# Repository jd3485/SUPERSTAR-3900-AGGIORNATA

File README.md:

# SUPERSTAR 3900 CON AGGIORNAMENTI

**Progetto radio Connex / Superstar 3900 aggiornato · due PCB THT MAIN + FRONT · KiCad · montaggio manuale PCBWay**

> **STATO 19 novembre 2026 — CAD CANDIDATO, NON FABBRICABILE.** La home `main` contiene documentazione e indici. Schemi e PCB effettivi si trovano nella [PR #1 in bozza](https://github.com/jd3485/SUPERSTAR-3900-AGGIORNATA/pull/1), ramo `cad/avvio-main-front`. **Non ancora integrati su main.**

## Cruscotto avanzamento

| Area | Stato verificato | Percorso |
|---|---|---|
| Mandato / regole | Documentazione integrata su `main` | [AGENTS.md](AGENTS.md) |
| Specifiche funzionali | REQ-01–14 **candidate sul ramo PR** | [Indice specifiche](01_Specifiche/README.md) |
| PCB MAIN | Schema e PCB candidate; **44 impronte THT presenti**, 18 ancora mancanti nel checkpoint | [Indice KiCad](KiCad/README.md) |
| PCB FRONT | Schema e PCB candidate; **4 componenti** posizionati e collegati | [Indice KiCad](KiCad/README.md) |
| Filtri RX / conversione / IF AM | Primi stadi progettati, modelli e netlist preliminari; non validati al banco | [Percorso RX candidato](https://github.com/jd3485/SUPERSTAR-3900-AGGIORNATA/tree/cad/avvio-main-front/KiCad/RX) |
| Sintonia | Mappa candidata di 240 canali base; estensioni a 271 da verificare | [Sintonia candidata](https://github.com/jd3485/SUPERSTAR-3900-AGGIORNATA/tree/cad/avvio-main-front/KiCad/Sintonia) |
| Verifiche CAD | **ERC MAIN 10 errori; FRONT 4**; DRC diagnostici, non finali | [Indice verifiche](Verifiche/README.md) |
| PCBWay / prototipo | **NON AUTORIZZATO**; nessuna PCB produttiva pronta | [Sicurezza](AGENTS.md#sicurezza) |

I numeri della MAIN/FRONT riportano l'**ultimo checkpoint del ramo candidato**, non la versione approvata di `main`. Un pad collegato nel layout parziale non equivale a scheda completa o validata.

## Versioni / milestone

| Milestone | Descrizione | Stato |
|---|---|---|
| **V0.0 — Bootstrap** | Direttiva, checkpoint, ingresso di ripresa | **Su `main`** |
| **V0.1 — MAIN/FRONT WIP** | Requisiti, primi schemi, prime PCB, PTT, alimentazione logica, RX/IF | **PR #1 DRAFT, NON MERGED** |
| **V0.2 — Integrazione tecnica** | Completamento dei percorsi e delle interfacce, qualifiche e regressioni | **Da realizzare** |
| **V1.0 — CAD pronto alla revisione di fabbricazione** | Schemi e PCB complete, ERC/DRC applicabili, BOM OEM, verifica indipendente | **Non raggiunta** |

Queste sigle sono **milestone organizzative** e non indicano versioni CAD rilasciate. La storia tecnica resta nei commit, nella PR e nel checkpoint.

## Navigazione repository

- [00_Gestione_Progetto — stato canonico e direttive](00_Gestione_Progetto/WORK_STATO_CORRENTE.md)
- [01_Specifiche — requisiti e decisioni](01_Specifiche/README.md)
- [KiCad — MAIN / FRONT / RX / Sintonia](KiCad/README.md)
- [Verifiche — ERC, netlist, DRC, modelli](Verifiche/README.md)
- [AGENTS.md — mandato, controlli e autorizzazioni](AGENTS.md)
- [PR #1 — lavoro CAD in corso](https://github.com/jd3485/SUPERSTAR-3900-AGGIORNATA/pull/1)

## Prossimi passi

Completare la catena RF/IF e la scelta del dispositivo RF THT secondo rumore, blocco e intermodulazione; chiudere alimentazioni, PTT e connessioni tra schede; trasferire sul PCB le impronte mancanti; qualificare componenti OEM attivi; correggere gli ERC, completare le PCB e verificare i DRC. Integrare la PR solo rispettando i gate e le autorizzazioni previsti.

**Vincoli permanenti:** NO FAB · NO GERBER DI PRODUZIONE · NO ORDINI PCB · NO TX · NO BATTERIA · NO VEICOLO, finché non espressamente autorizzati dopo le verifiche.

### Ripresa da una nuova chat

«Riprendi `jd3485/SUPERSTAR-3900-AGGIORNATA` da `main`, leggi `AGENTS.md`, `00_Gestione_Progetto/WORK_STATO_CORRENTE.md` e la PR aperta, verifica lo SHA reale e procedi».

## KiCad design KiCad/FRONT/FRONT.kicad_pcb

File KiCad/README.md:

# KiCad — Schemi e PCB native

**Su `main`:** nessuna scheda CAD integrata al momento di questo indice.

**Su ramo candidato [`cad/avvio-main-front`](https://github.com/jd3485/SUPERSTAR-3900-AGGIORNATA/tree/cad/avvio-main-front/KiCad):**

- [MAIN — schema](https://github.com/jd3485/SUPERSTAR-3900-AGGIORNATA/blob/cad/avvio-main-front/KiCad/MAIN/MAIN.kicad_sch) · [MAIN — PCB](https://github.com/jd3485/SUPERSTAR-3900-AGGIORNATA/blob/cad/avvio-main-front/KiCad/MAIN/MAIN.kicad_pcb)
- [FRONT — schema](https://github.com/jd3485/SUPERSTAR-3900-AGGIORNATA/blob/cad/avvio-main-front/KiCad/FRONT/FRONT.kicad_sch) · [FRONT — PCB](https://github.com/jd3485/SUPERSTAR-3900-AGGIORNATA/blob/cad/avvio-main-front/KiCad/FRONT/FRONT.kicad_pcb)
- [Percorso RX/IF](https://github.com/jd3485/SUPERSTAR-3900-AGGIORNATA/tree/cad/avvio-main-front/KiCad/RX) · [Sintonia](https://github.com/jd3485/SUPERSTAR-3900-AGGIORNATA/tree/cad/avvio-main-front/KiCad/Sintonia) · [Interfaccia MAIN–FRONT](https://github.com/jd3485/SUPERSTAR-3900-AGGIORNATA/blob/cad/avvio-main-front/KiCad/INTERFACCIA_MAIN_FRONT.md)

**Non fabbricabile:** contorni, componenti, connessioni, alimentazioni, ERC e qualifica ancora incompleti. Nessun Gerber produttivo autorizzato.

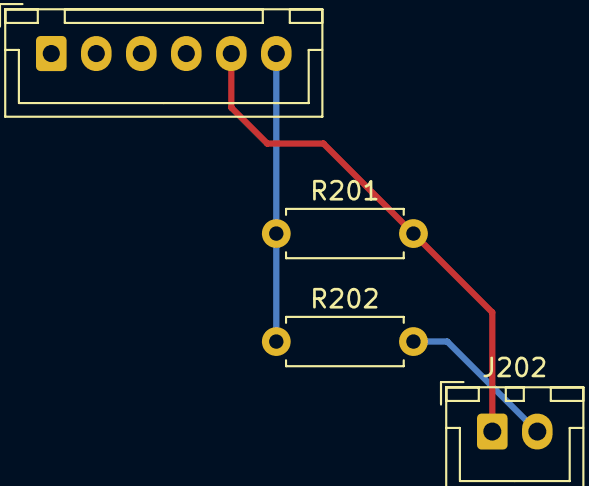
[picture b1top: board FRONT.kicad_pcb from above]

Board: 2 copper layers, 4 parts (0 on the bottom side), 3 nets.

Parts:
J201: Conn_01x06; JST_XH_B6B-XH-A_1x06_P2.50mm_Vertical
J202: Conn_01x02; JST_XH_B2B-XH-A_1x02_P2.50mm_Vertical
R201: 10k; R_Axial_DIN0207_L6.3mm_D2.5mm_P7.62mm_Horizontal
R202: 2.2k; R_Axial_DIN0207_L6.3mm_D2.5mm_P7.62mm_Horizontal

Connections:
/CONTROL_RETURN: J201.5, J202.1, R201.2
/MIC_PTT_KEY: J202.2, R202.2
/PTT_SENSE: J201.6, R201.1, R202.1

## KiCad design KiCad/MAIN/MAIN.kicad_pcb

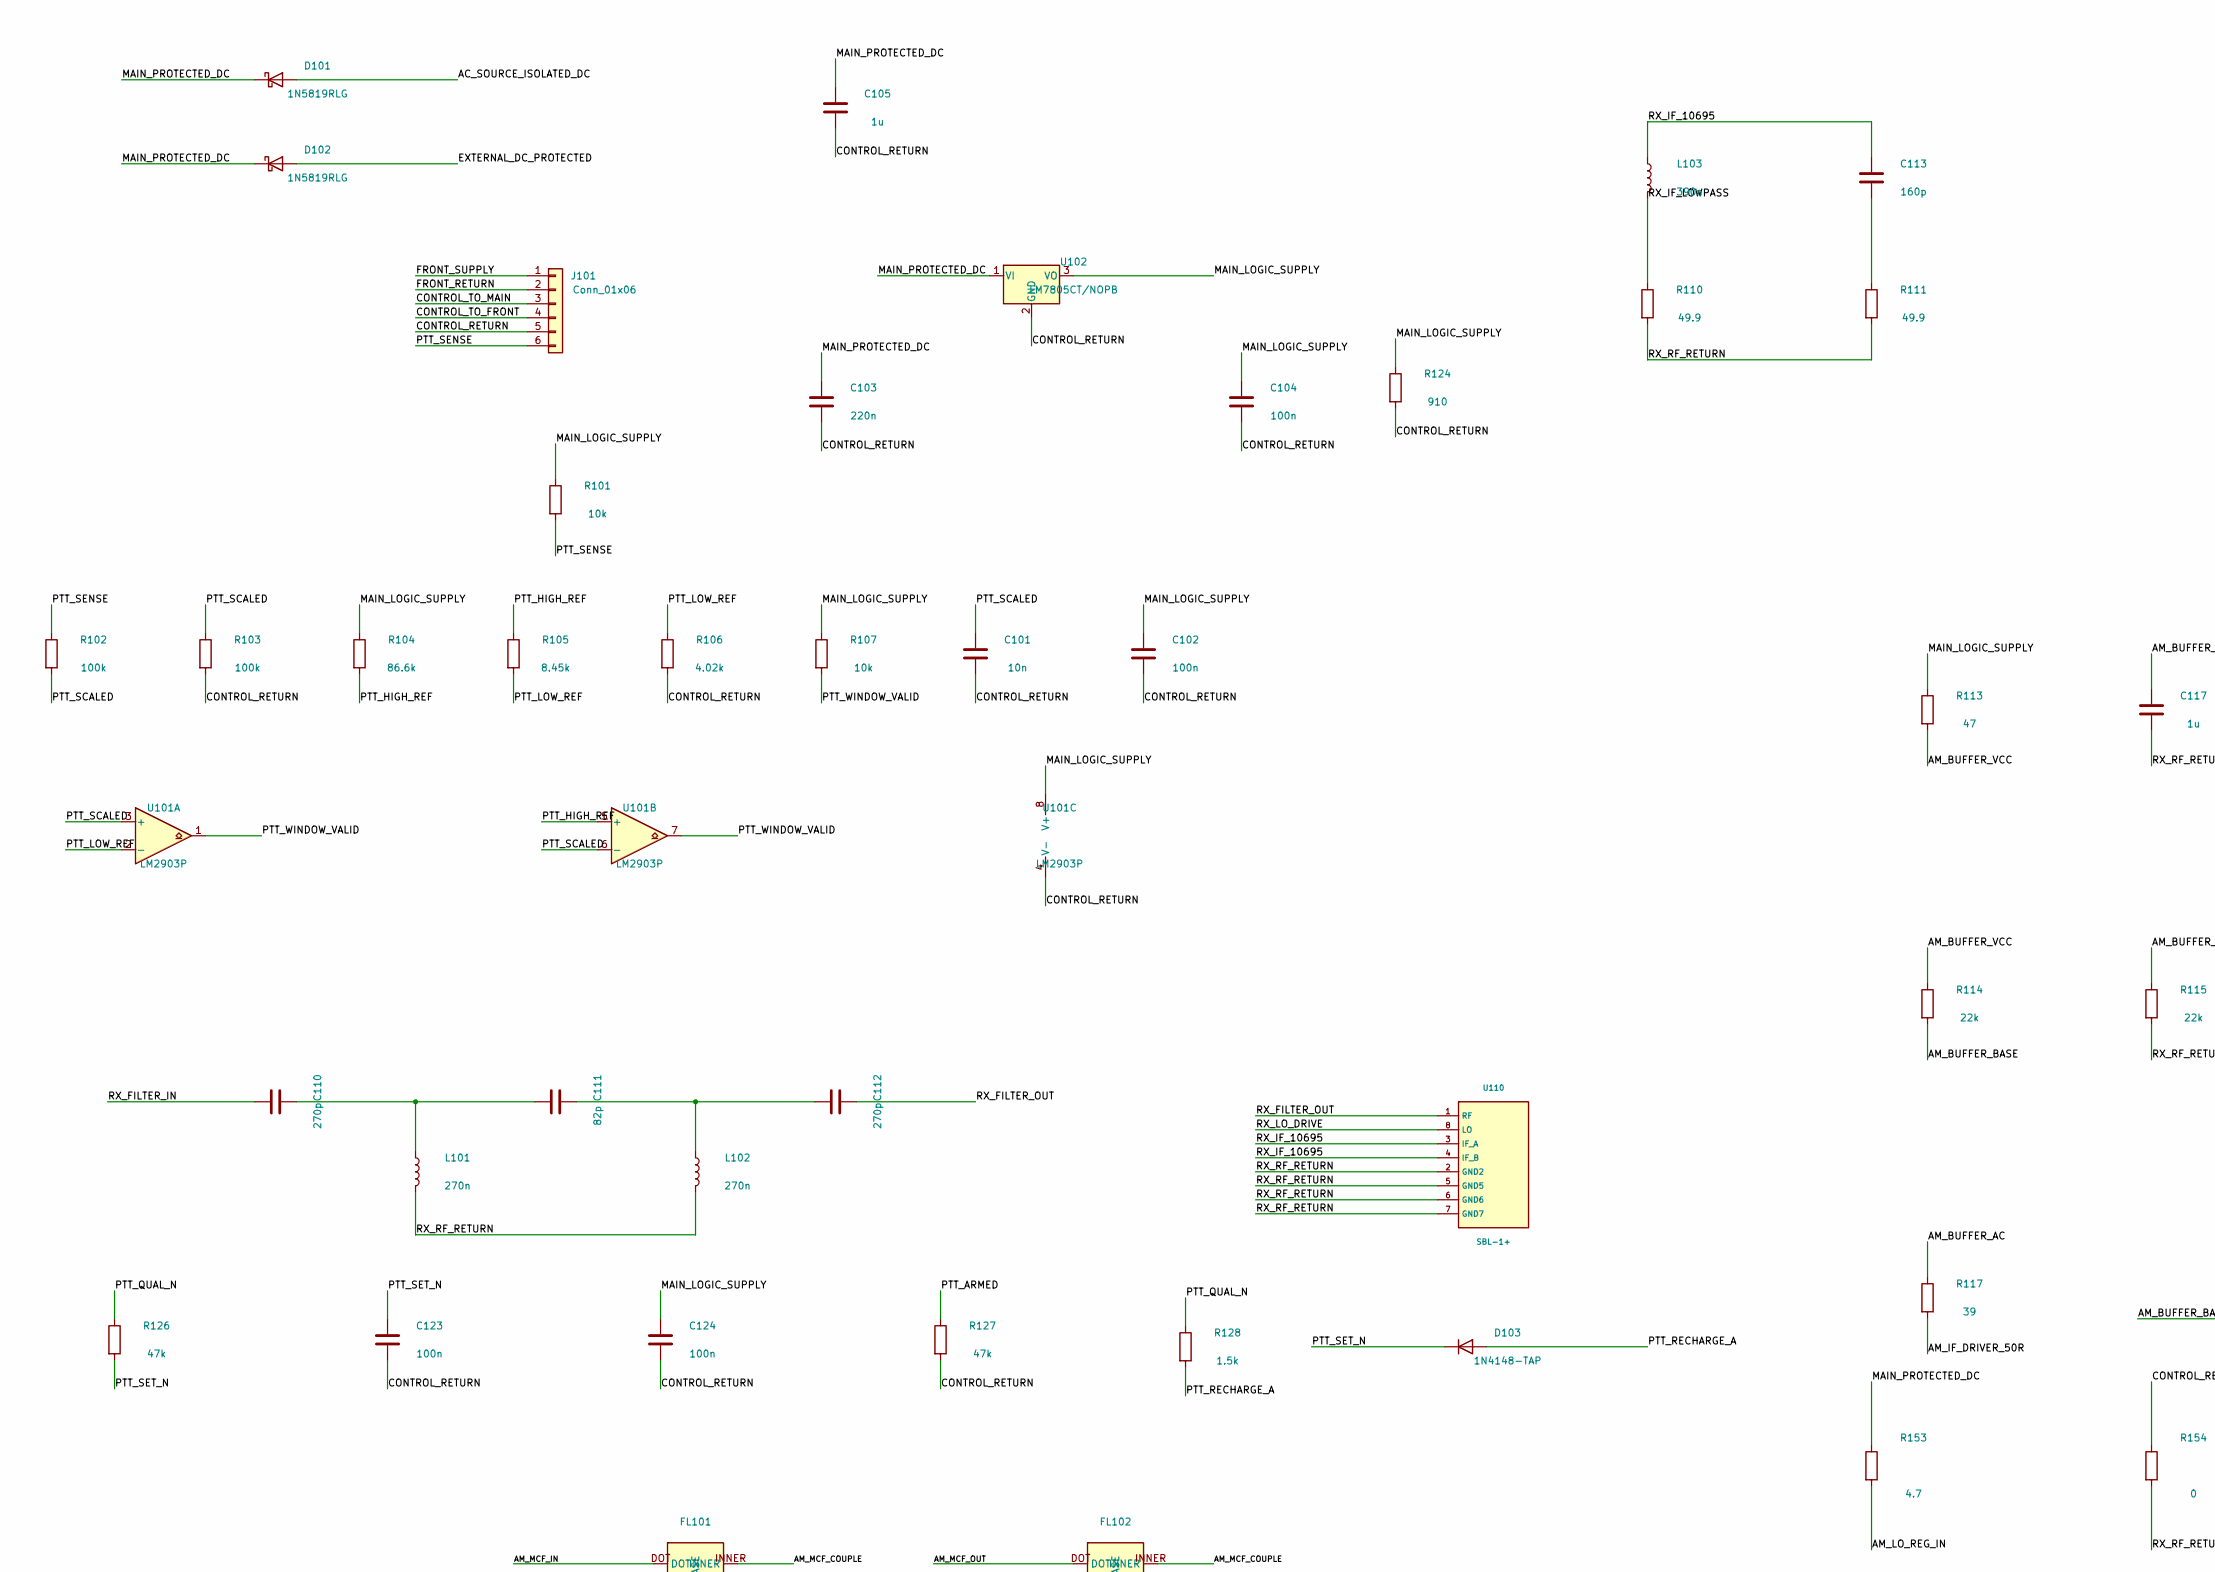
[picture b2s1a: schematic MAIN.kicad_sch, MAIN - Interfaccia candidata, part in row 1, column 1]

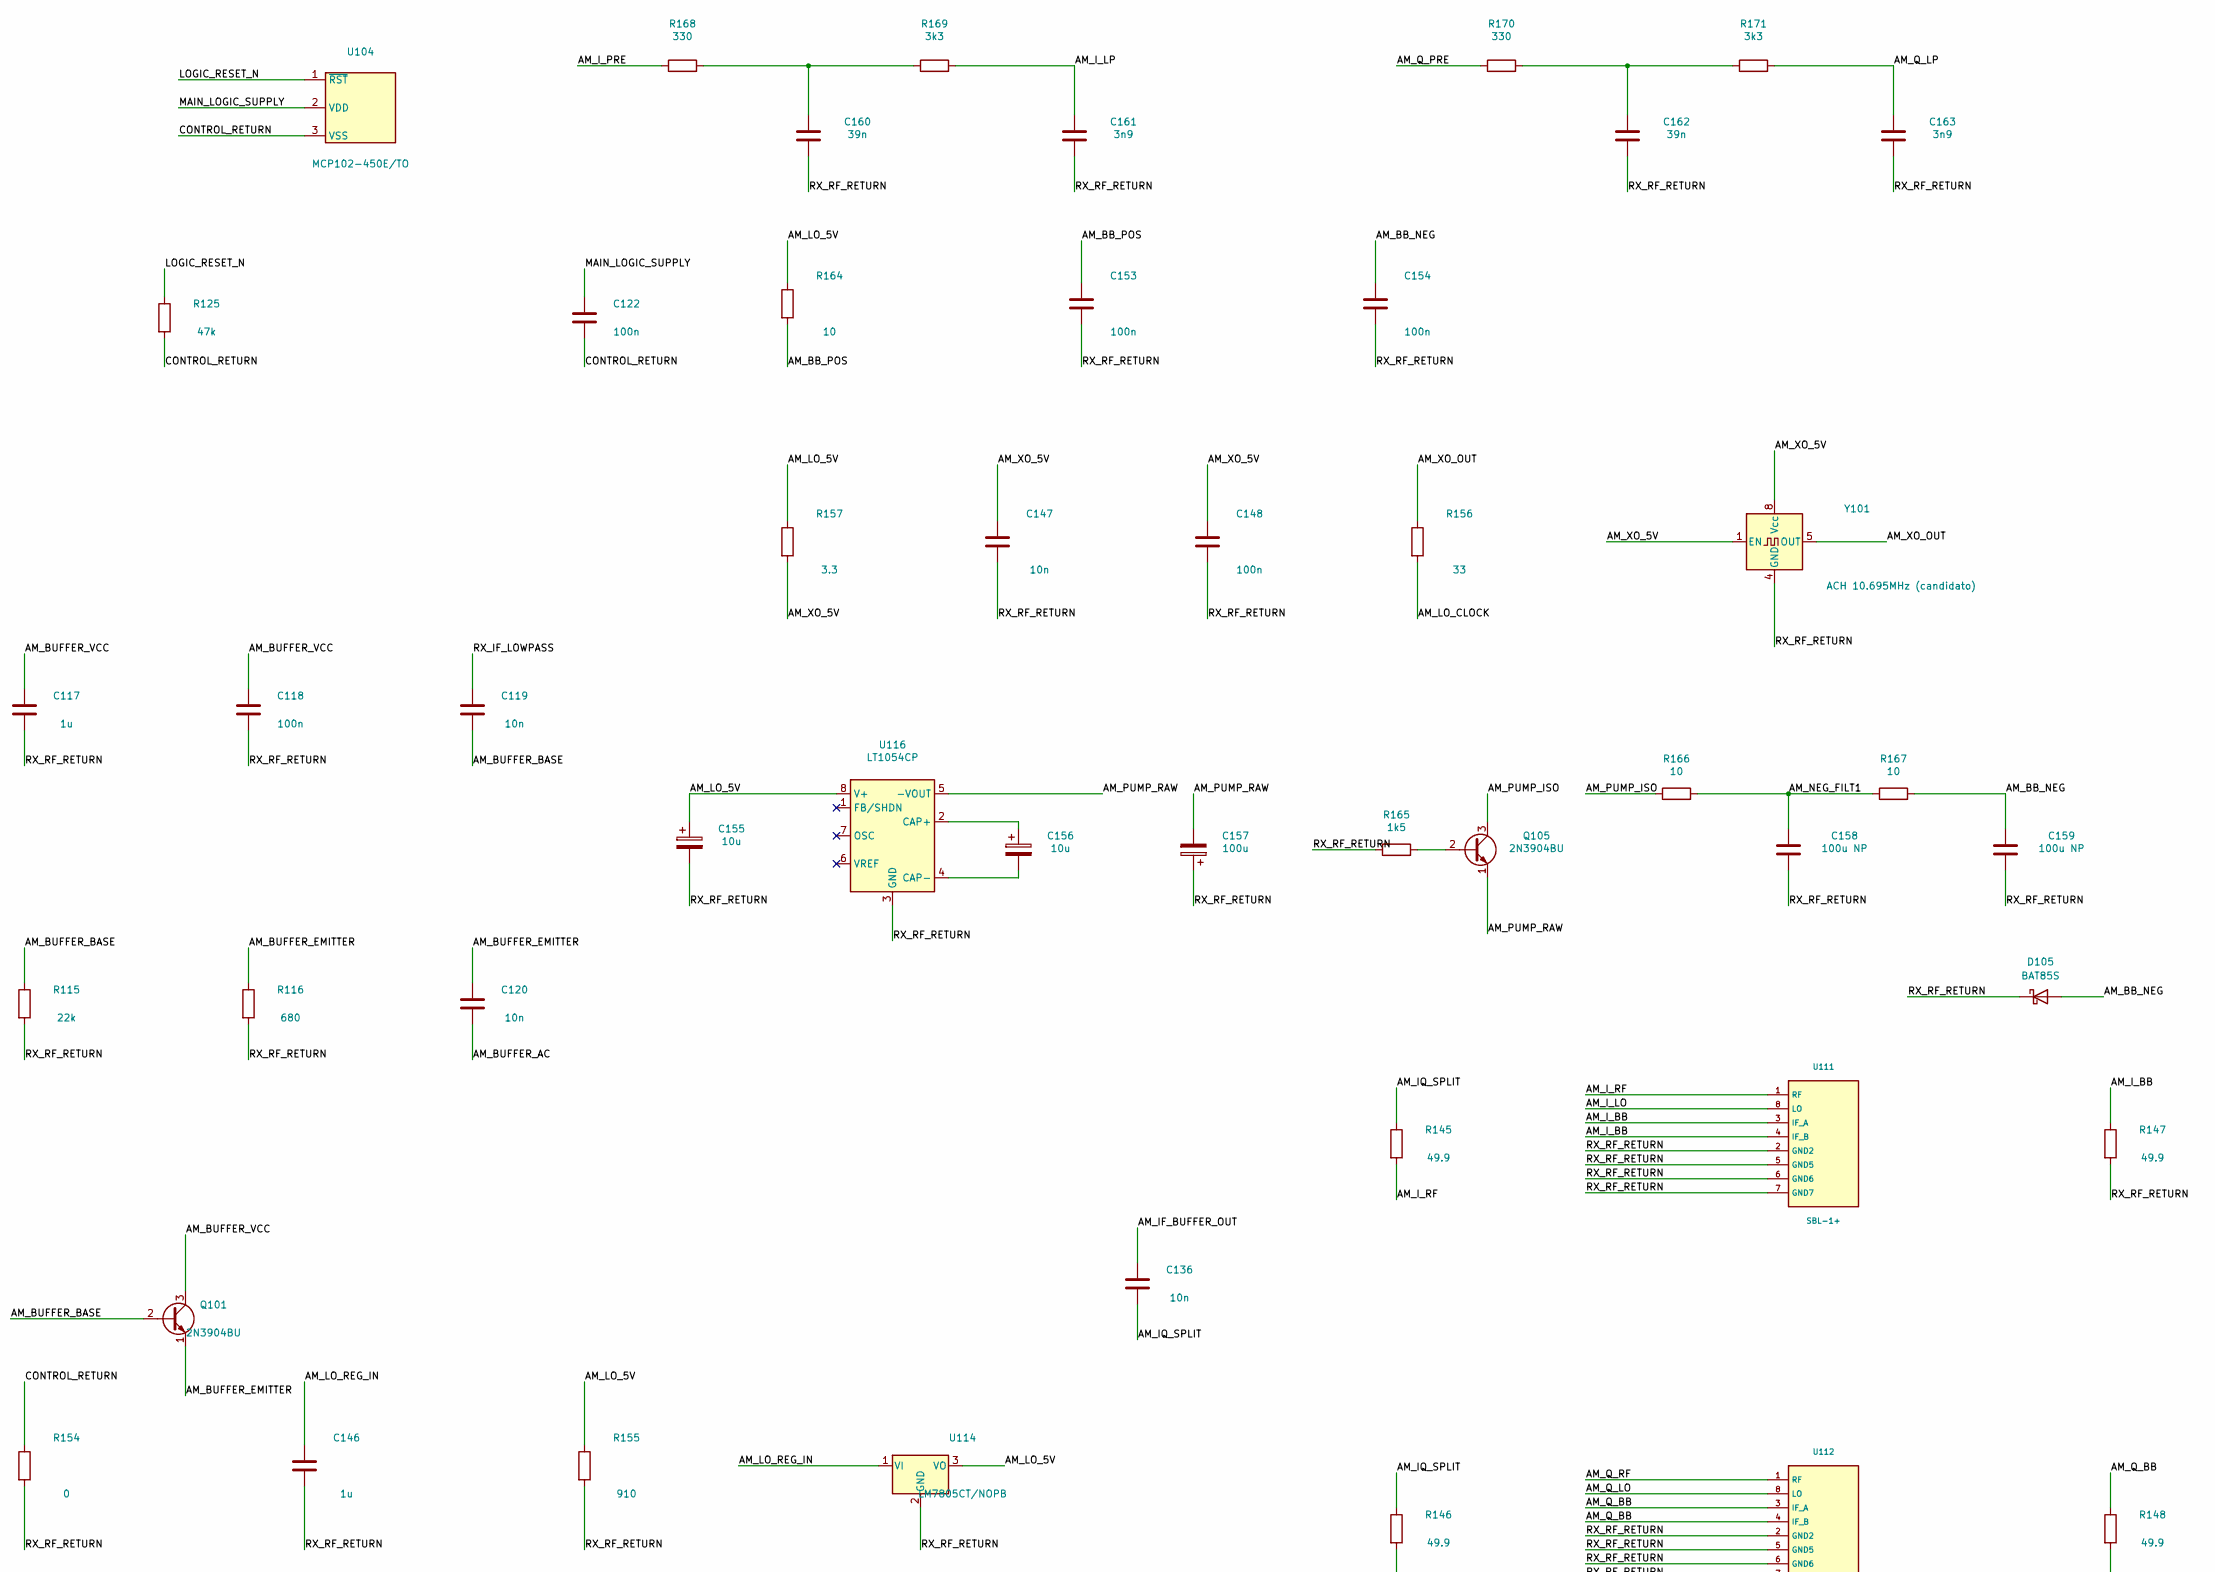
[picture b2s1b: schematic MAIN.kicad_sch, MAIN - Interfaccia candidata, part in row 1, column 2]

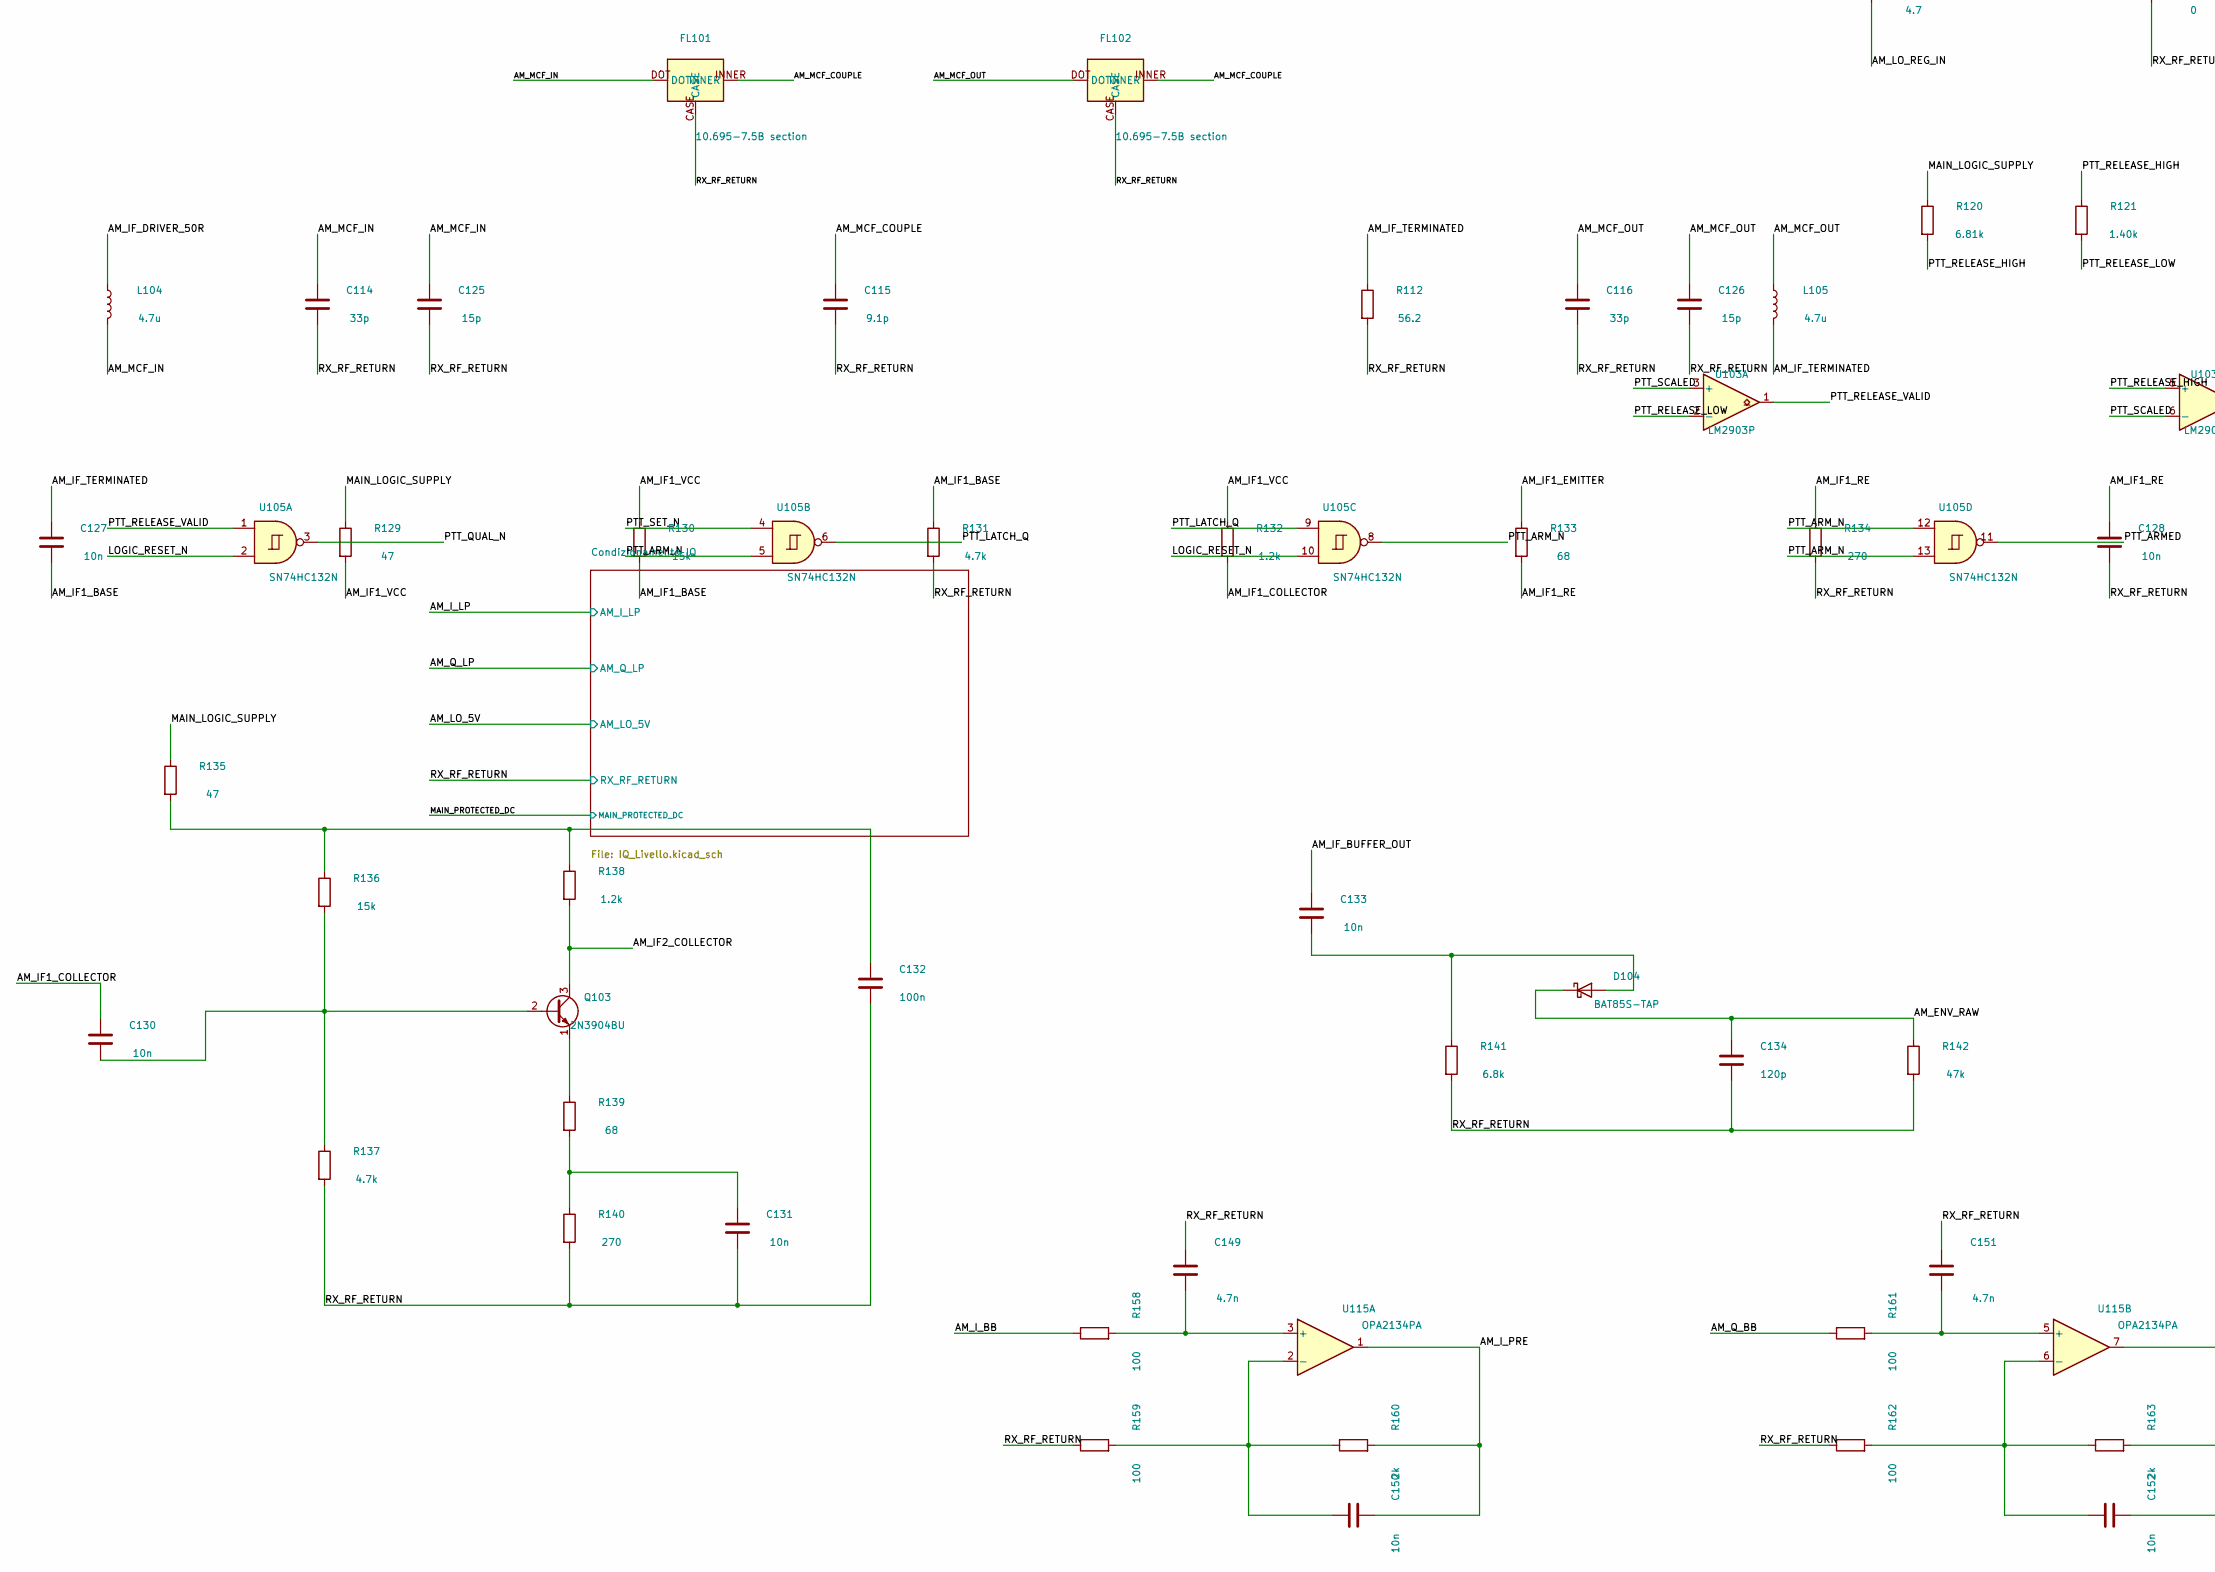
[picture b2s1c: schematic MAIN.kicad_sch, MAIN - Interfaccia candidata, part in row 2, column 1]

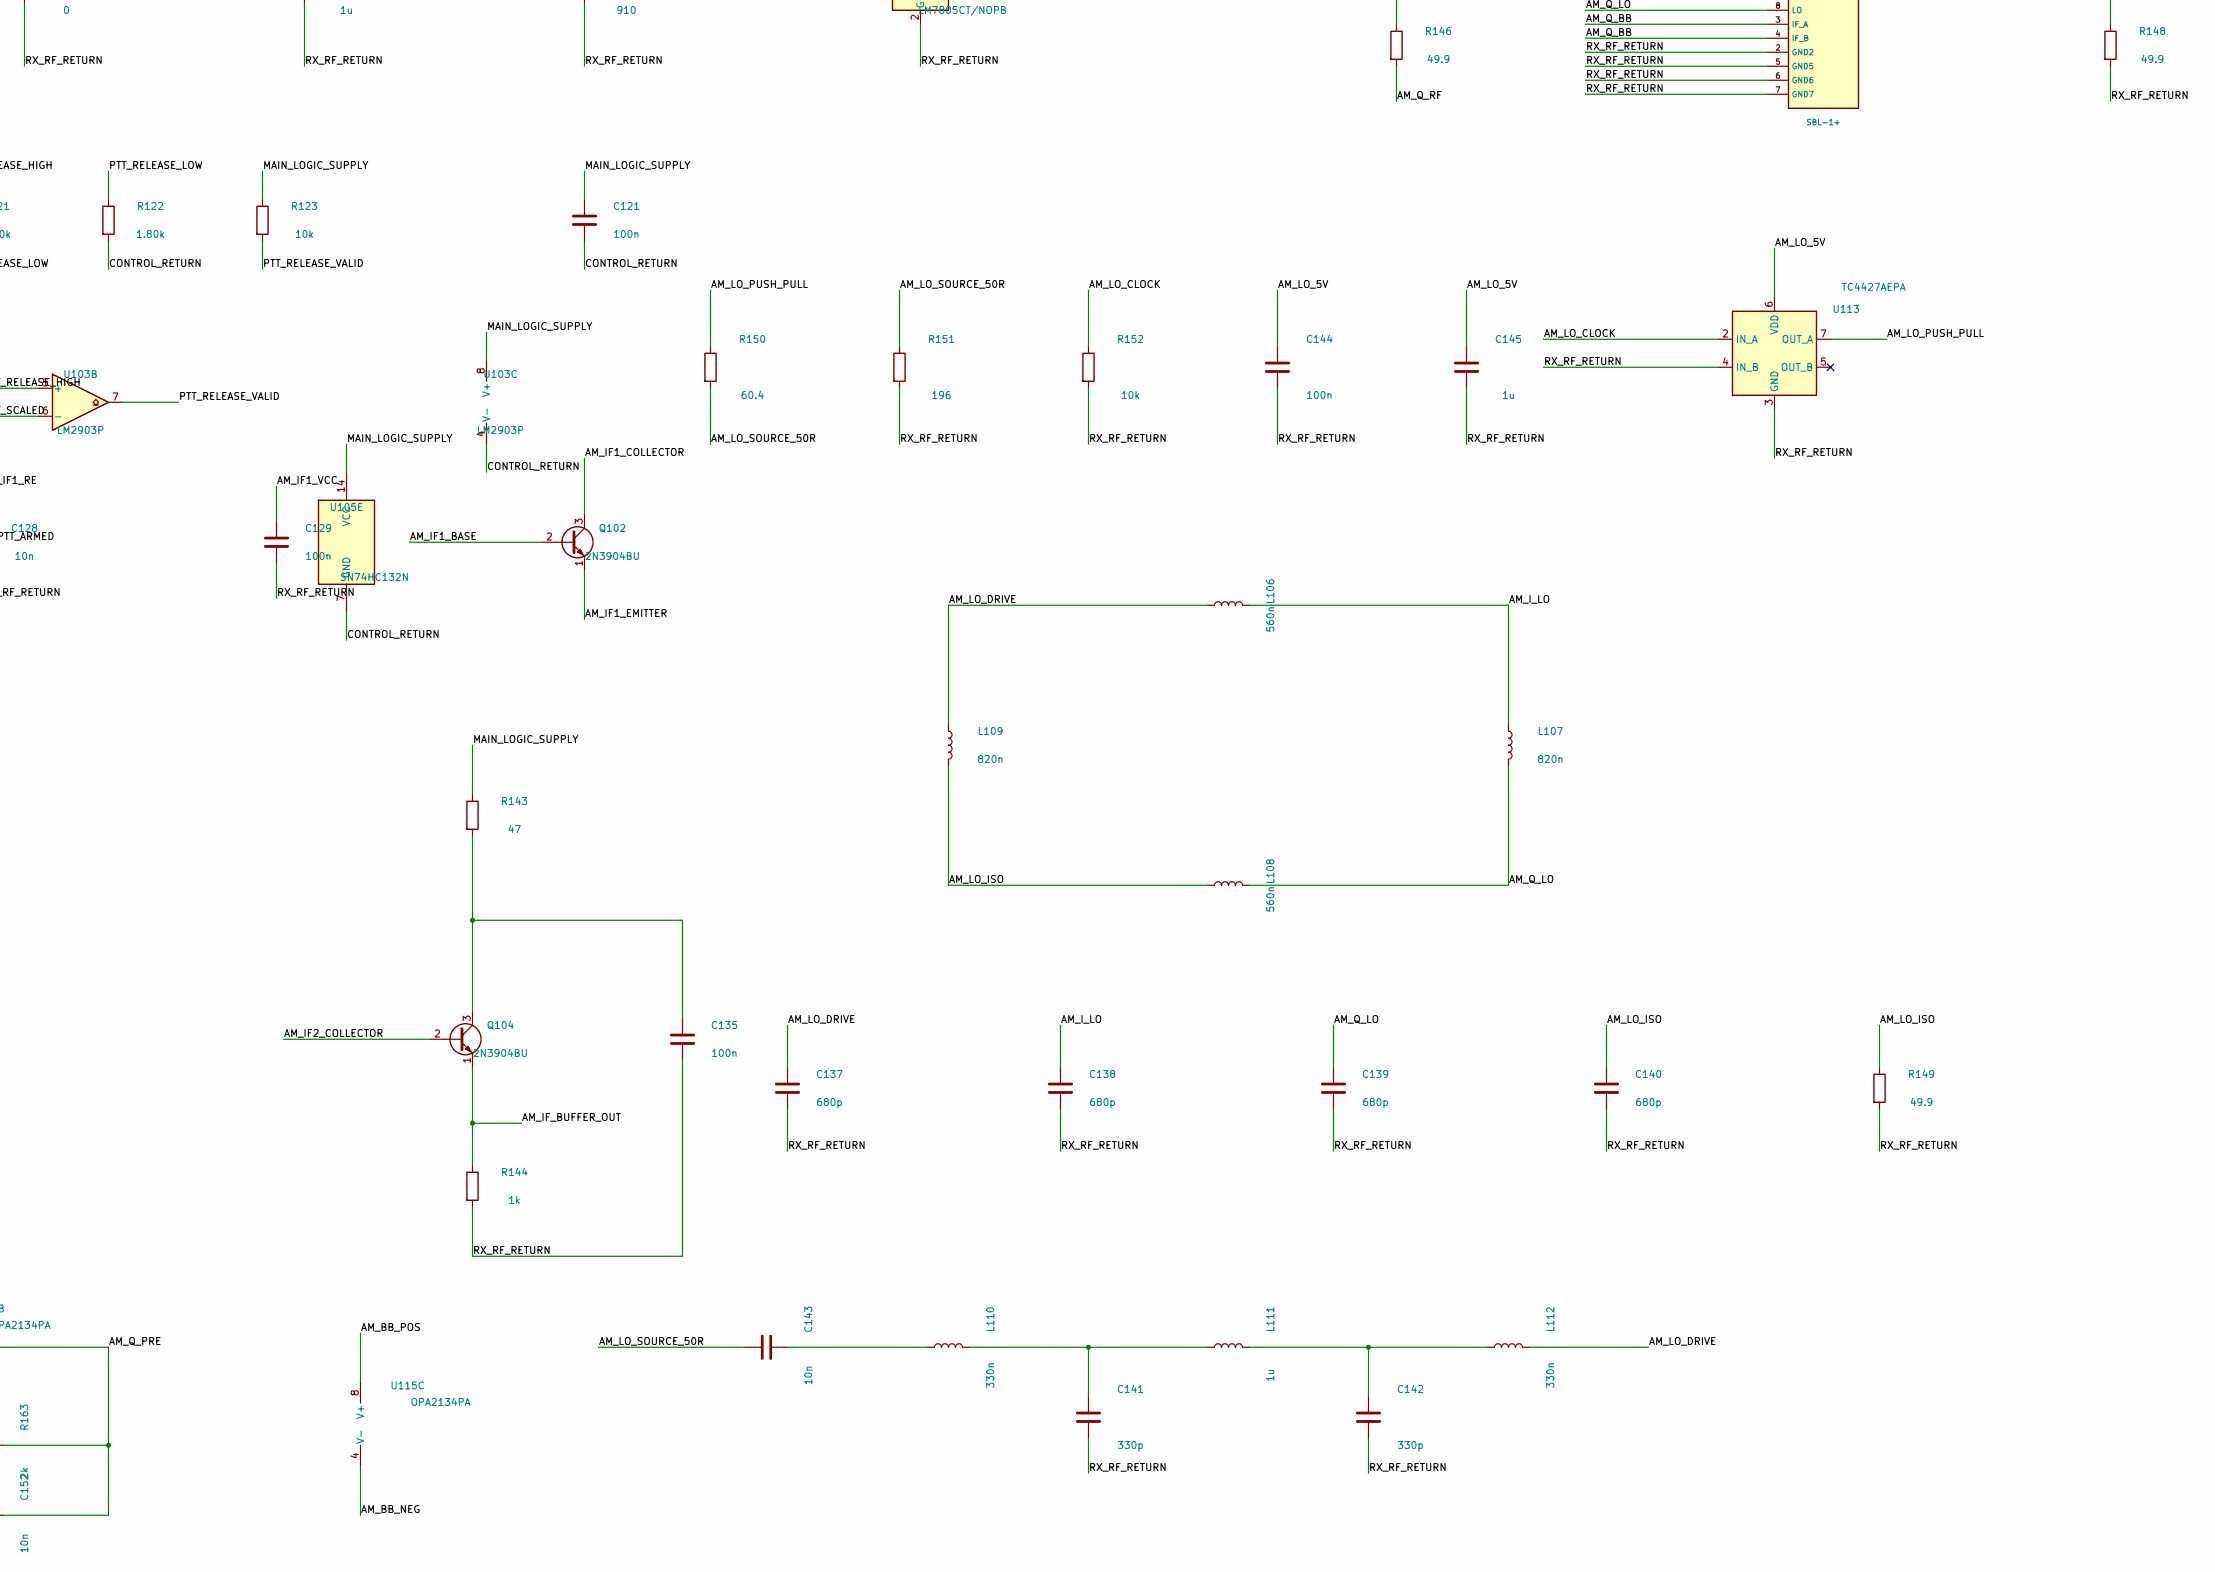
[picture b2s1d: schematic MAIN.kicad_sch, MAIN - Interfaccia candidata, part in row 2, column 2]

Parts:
C101, C119, C120, C127, C128, C130, C131, C133, C136, C143, C147, C150, C152: 10n; C_Rect_L4.0mm_W2.5mm_P2.50mm
C102, C104, C118, C121, C122, C123, C124, C129, C132, C135, C144, C148, C153, C154: 100n; C_Rect_L4.0mm_W2.5mm_P2.50mm
C103: 220n; C_Rect_L4.0mm_W2.5mm_P2.50mm
C105, C117, C146: 1u; C_Rect_L7.0mm_W4.5mm_P5.00mm
C110, C112: 270p; C_Rect_L4.0mm_W2.5mm_P2.50mm
C111: 82p; C_Rect_L4.0mm_W2.5mm_P2.50mm
C113: 160p; C_Rect_L4.0mm_W2.5mm_P2.50mm
C114, C116: 33p; C_Rect_L4.0mm_W2.5mm_P2.50mm
C115: 9.1p; C_Rect_L4.0mm_W2.5mm_P2.50mm
C125, C126: 15p; C_Rect_L4.0mm_W2.5mm_P2.50mm
C134: 120p; C_Rect_L4.0mm_W2.5mm_P2.50mm
C137, C138, C139, C140: 680p; C_Rect_L4.0mm_W2.5mm_P2.50mm
C141, C142: 330p; C_Rect_L4.0mm_W2.5mm_P2.50mm
C145: 1u; C_Rect_L4.0mm_W2.5mm_P2.50mm
C149, C151: 4.7n; C_Rect_L4.0mm_W2.5mm_P2.50mm
C155, C156: 10u; CP_Radial_D5.0mm_P2.00mm
C157: 100u; CP_Radial_D6.3mm_P2.50mm
C158, C159: 100u NP; C_Radial_D10.0mm_H16.0mm_P5.00mm
C160, C162: 39n; C_Rect_L7.0mm_W2.5mm_P5.00mm
C161, C163: 3n9; C_Rect_L7.0mm_W2.5mm_P5.00mm
D101, D102: 1N5819RLG; D_DO-41_SOD81_P7.62mm_Horizontal
D103: 1N4148-TAP; D_DO-35_SOD27_P7.62mm_Horizontal
D104: BAT85S-TAP; D_DO-35_SOD27_P7.62mm_Horizontal
D105: BAT85S; D_DO-35_SOD27_P7.62mm_Horizontal
FL101, FL102: 10.695-7.5B section; Krystaly_HC49U_3pin_MCF
J101: Conn_01x06; JST_XH_B6B-XH-A_1x06_P2.50mm_Vertical
L101, L102: 270n; L_Axial_L7.0mm_D3.3mm_P10.16mm_Horizontal_Fastron_MICC
L103: 390n; L_Axial_L9.5mm_D4.0mm_P12.70mm_Horizontal_Fastron_SMCC
L104, L105: 4.7u; L_Axial_L7.0mm_D3.3mm_P10.16mm_Horizontal_Fastron_MICC
L106, L108: 560n; L_Axial_L7.0mm_D3.3mm_P10.16mm_Horizontal_Fastron_MICC
L107, L109: 820n; L_Axial_L7.0mm_D3.3mm_P10.16mm_Horizontal_Fastron_MICC
L110, L112: 330n; L_Axial_L7.0mm_D3.3mm_P10.16mm_Horizontal_Fastron_MICC
L111: 1u; L_Axial_L7.0mm_D3.3mm_P10.16mm_Horizontal_Fastron_MICC
Q101, Q102, Q103, Q104, Q105: 2N3904BU; TO-92_Inline
R101, R107, R123, R152: 10k; R_Axial_DIN0207_L6.3mm_D2.5mm_P7.62mm_Horizontal
R102, R103: 100k; R_Axial_DIN0207_L6.3mm_D2.5mm_P7.62mm_Horizontal
R104: 86.6k; R_Axial_DIN0207_L6.3mm_D2.5mm_P7.62mm_Horizontal
R105: 8.45k; R_Axial_DIN0207_L6.3mm_D2.5mm_P7.62mm_Horizontal
R106: 4.02k; R_Axial_DIN0207_L6.3mm_D2.5mm_P7.62mm_Horizontal
R110, R111, R145, R146, R147, R148, R149: 49.9; R_Axial_DIN0207_L6.3mm_D2.5mm_P7.62mm_Horizontal
R112: 56.2; R_Axial_DIN0207_L6.3mm_D2.5mm_P7.62mm_Horizontal
R113, R129, R135, R143: 47; R_Axial_DIN0207_L6.3mm_D2.5mm_P7.62mm_Horizontal
R114, R115: 22k; R_Axial_DIN0207_L6.3mm_D2.5mm_P7.62mm_Horizontal
R116: 680; R_Axial_DIN0207_L6.3mm_D2.5mm_P7.62mm_Horizontal
R117: 39; R_Axial_DIN0207_L6.3mm_D2.5mm_P7.62mm_Horizontal
R120: 6.81k; R_Axial_DIN0207_L6.3mm_D2.5mm_P7.62mm_Horizontal
R121: 1.40k; R_Axial_DIN0207_L6.3mm_D2.5mm_P7.62mm_Horizontal
R122: 1.80k; R_Axial_DIN0207_L6.3mm_D2.5mm_P7.62mm_Horizontal
R124, R155: 910; R_Axial_DIN0207_L6.3mm_D2.5mm_P7.62mm_Horizontal
R125, R126, R127, R142: 47k; R_Axial_DIN0207_L6.3mm_D2.5mm_P7.62mm_Horizontal
R128: 1.5k; R_Axial_DIN0207_L6.3mm_D2.5mm_P7.62mm_Horizontal
R130, R136: 15k; R_Axial_DIN0207_L6.3mm_D2.5mm_P7.62mm_Horizontal
R131, R137: 4.7k; R_Axial_DIN0207_L6.3mm_D2.5mm_P7.62mm_Horizontal
R132, R138: 1.2k; R_Axial_DIN0207_L6.3mm_D2.5mm_P7.62mm_Horizontal
R133, R139: 68; R_Axial_DIN0207_L6.3mm_D2.5mm_P7.62mm_Horizontal
R134, R140: 270; R_Axial_DIN0207_L6.3mm_D2.5mm_P7.62mm_Horizontal
R141: 6.8k; R_Axial_DIN0207_L6.3mm_D2.5mm_P7.62mm_Horizontal
R144: 1k; R_Axial_DIN0207_L6.3mm_D2.5mm_P7.62mm_Horizontal
R150: 60.4; R_Axial_DIN0207_L6.3mm_D2.5mm_P7.62mm_Horizontal
R151: 196; R_Axial_DIN0207_L6.3mm_D2.5mm_P7.62mm_Horizontal
R153: 4.7; R_Axial_DIN0207_L6.3mm_D2.5mm_P7.62mm_Horizontal
R154: 0; R_Axial_DIN0207_L6.3mm_D2.5mm_P7.62mm_Horizontal
R156: 33; R_Axial_DIN0207_L6.3mm_D2.5mm_P7.62mm_Horizontal
R157: 3.3; R_Axial_DIN0207_L6.3mm_D2.5mm_P7.62mm_Horizontal
R158, R159, R161, R162: 100; R_Axial_DIN0207_L6.3mm_D2.5mm_P7.62mm_Horizontal
R160, R163: 2k; R_Axial_DIN0207_L6.3mm_D2.5mm_P7.62mm_Horizontal
R164, R166, R167: 10; R_Axial_DIN0207_L6.3mm_D2.5mm_P7.62mm_Horizontal
R165: 1k5; R_Axial_DIN0207_L6.3mm_D2.5mm_P7.62mm_Horizontal
R168, R170: 330; R_Axial_DIN0207_L6.3mm_D2.5mm_P7.62mm_Horizontal
R169, R171: 3k3; R_Axial_DIN0207_L6.3mm_D2.5mm_P7.62mm_Horizontal
U101, U103: LM2903P; DIP-8_W7.62mm
U102, U114: LM7805CT/NOPB; TO-220-3_Vertical
U104: MCP102-450E/TO; TO-92_Inline
U105: SN74HC132N; DIP-14_W7.62mm
U110, U111, U112: SBL-1+; Mini-Circuits_A06
U113: TC4427AEPA; DIP-8_W7.62mm
U115: OPA2134PA; DIP-8_W7.62mm
U116: LT1054CP; DIP-8_W7.62mm
Y101: ACH 10.695MHz (candidato); Oscillator_DIP-8

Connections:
/AC_SOURCE_ISOLATED_DC: D101.2 (A)
/AM_BB_NEG: C154.1, C159.2, D105.2 (A), R167.2, U115.4 (V-)
/AM_BB_POS: C153.1, R164.2, U115.8 (V+)
/AM_BUFFER_AC: C120.2, R117.1
/AM_BUFFER_BASE: C119.2, Q101.2 (B), R114.2, R115.1
/AM_BUFFER_EMITTER: C120.1, Q101.1 (E), R116.1
/AM_BUFFER_VCC: C117.1, C118.1, Q101.3 (C), R113.2, R114.1
/AM_ENV_RAW: C134.1, D104.1 (K), R142.1
/AM_IF1_BASE: C127.2, Q102.2 (B), R130.2, R131.1
/AM_IF1_COLLECTOR: C130.1, Q102.3 (C), R132.2
/AM_IF1_EMITTER: Q102.1 (E), R133.1
/AM_IF1_RE: C128.1, R133.2, R134.1
/AM_IF1_VCC: C129.1, R129.2, R130.1, R132.1
/AM_IF2_COLLECTOR: Q103.3 (C), Q104.2 (B), R138.2
/AM_IF_BUFFER_OUT: C133.1, C136.1, Q104.1 (E), R144.1
/AM_IF_DRIVER_50R: L104.1, R117.2
/AM_IF_TERMINATED: C127.1, L105.2, R112.1
/AM_IQ_SPLIT: C136.2, R145.1, R146.1
/AM_I_BB: R147.1, R158.1, U111.3 (IF_A), U111.4 (IF_B)
/AM_I_LO: C138.1, L106.2, L107.1, U111.8 (LO)
/AM_I_LP: C161.1, R169.2; also elsewhere on the board
/AM_I_PRE: C150.2, R160.2, R168.1, U115.1
/AM_I_RF: R145.2, U111.1 (RF)
/AM_LO_5V: C144.1, C145.1, C155.1, R155.1, R157.1, R164.1, U113.6 (VDD), U114.3 (VO), U116.8 (V+); also elsewhere on the board
/AM_LO_CLOCK: R152.1, R156.2, U113.2 (IN_A)
/AM_LO_DRIVE: C137.1, L106.1, L109.1, L112.2
/AM_LO_ISO: C140.1, L108.1, L109.2, R149.1
/AM_LO_PUSH_PULL: R150.1, U113.7 (OUT_A)
/AM_LO_REG_IN: C146.1, R153.2, U114.1 (VI)
/AM_LO_SOURCE_50R: C143.1, R150.2, R151.1
/AM_MCF_COUPLE: C115.1, FL101.INNER, FL102.INNER
/AM_MCF_IN: C114.1, C125.1, FL101.DOT, L104.2
/AM_MCF_OUT: C116.1, C126.1, FL102.DOT, L105.1
/AM_NEG_FILT1: C158.2, R166.2, R167.1
/AM_PUMP_ISO: Q105.3 (C), R166.1
/AM_PUMP_RAW: C157.2, Q105.1 (E), U116.5 (-VOUT)
/AM_Q_BB: R148.1, R161.1, U112.3 (IF_A), U112.4 (IF_B)
/AM_Q_LO: C139.1, L107.2, L108.2, U112.8 (LO)
/AM_Q_LP: C163.1, R171.2; also elsewhere on the board
/AM_Q_PRE: C152.2, R163.2, R170.1, U115.7
/AM_Q_RF: R146.2, U112.1 (RF)
/AM_XO_5V: C147.1, C148.1, R157.2, Y101.1 (EN), Y101.8 (Vcc)
/AM_XO_OUT: R156.1, Y101.5 (OUT)
/CONTROL_RETURN: C101.2, C102.2, C103.2, C104.2, C105.2, C121.2, C122.2, C123.2, C124.2, J101.5, R103.2, R106.2, R122.2, R124.2, R125.2, R127.2, R154.1, U101.4 (V-), U102.2 (GND), U103.4 (V-), U104.3 (VSS), U105.7 (GND)
/CONTROL_TO_FRONT: J101.4
/CONTROL_TO_MAIN: J101.3
/EXTERNAL_DC_PROTECTED: D102.2 (A)
/FRONT_RETURN: J101.2
/FRONT_SUPPLY: J101.1
/LOGIC_RESET_N: R125.1, U104.1 (~RST), U105.2, U105.10
/MAIN_LOGIC_SUPPLY: C102.1, C104.1, C121.1, C122.1, C124.1, R101.1, R104.1, R107.1, R113.1, R120.1, R123.1, R124.1, R129.1, R135.1, R143.1, U101.8 (V+), U102.3 (VO), U103.8 (V+), U104.2 (VDD), U105.14 (VCC)
/MAIN_PROTECTED_DC: C103.1, C105.1, D101.1 (K), D102.1 (K), R153.1, U102.1 (VI); also elsewhere on the board
/PTT_ARMED: R127.1, U105.11
/PTT_ARM_N: U105.5, U105.8, U105.12, U105.13
/PTT_HIGH_REF: R104.2, R105.1, U101.5 (+)
/PTT_LATCH_Q: U105.6, U105.9
/PTT_LOW_REF: R105.2, R106.1, U101.2 (-)
/PTT_QUAL_N: R126.1, R128.1, U105.3
/PTT_RECHARGE_A: D103.2 (A), R128.2
/PTT_RELEASE_HIGH: R120.2, R121.1, U103.5 (+)
/PTT_RELEASE_LOW: R121.2, R122.1, U103.2 (-)
/PTT_RELEASE_VALID: R123.2, U103.1, U103.7, U105.1
/PTT_SCALED: C101.1, R102.2, R103.1, U101.3 (+), U101.6 (-), U103.3 (+), U103.6 (-)
/PTT_SENSE: J101.6, R101.2, R102.1
/PTT_SET_N: C123.1, D103.1 (K), R126.2, U105.4
/PTT_WINDOW_VALID: R107.2, U101.1, U101.7
/RX_FILTER_IN: C110.1
/RX_FILTER_OUT: C112.2, U110.1 (RF)
/RX_IF_10695: C113.1, L103.1, U110.3 (IF_A), U110.4 (IF_B)
/RX_IF_LOWPASS: C119.1, L103.2, R110.1
/RX_LO_DRIVE: U110.8 (LO)
/RX_RF_RETURN: C114.2, C115.2, C116.2, C117.2, C118.2, C125.2, C126.2, C128.2, C129.2, C131.2, C132.2, C134.2, C135.2, C137.2, C138.2, C139.2, C140.2, C141.2, C142.2, C144.2, C145.2, C146.2, C147.2, C148.2, C149.1, C151.1, C153.2, C154.2, C155.2, C157.1, C158.1, C159.1, C160.2, C161.2, C162.2, C163.2, D105.1 (K), FL101.CASE, FL102.CASE, L101.2, L102.2, R110.2, R111.2, R112.2, R115.2, R116.2, R131.2, R134.2, R137.2, R140.2, R141.2, R142.2, R144.2, R147.2, R148.2, R149.2, R151.2, R152.2, R154.2, R155.2, R159.1, R162.1, R165.1, U110.2 (GND2), U110.5 (GND5), U110.6 (GND6), U110.7 (GND7), U111.2 (GND2), U111.5 (GND5), U111.6 (GND6), U111.7 (GND7), U112.2 (GND2), U112.5 (GND5), U112.6 (GND6), U112.7 (GND7), U113.3 (GND), U113.4 (IN_B), U114.2 (GND), U116.3 (GND), Y101.4 (GND); also elsewhere on the board
unnamed: C110.2, C111.1, L101.1
unnamed: C111.2, C112.1, L102.1
unnamed: C113.2, R111.1
unnamed: C131.1, R139.2, R140.1
unnamed: C132.1, R135.2, R136.1, R138.1
unnamed: C141.1, L110.2, L111.1
unnamed: C142.1, L111.2, L112.1
unnamed: C143.2, L110.1
unnamed: C160.1, R168.2, R169.1
unnamed: C162.1, R170.2, R171.1
unnamed: C133.2, D104.2 (A), R141.1
unnamed: C130.2, Q103.2 (B), R136.2, R137.1
unnamed: Q103.1 (E), R139.1
unnamed: C135.1, Q104.3 (C), R143.2
unnamed: Q105.2 (B), R165.2
unnamed: C149.2, R158.2, U115.3 (+)
unnamed: C150.1, R159.2, R160.1, U115.2 (-)
unnamed: C151.2, R161.2, U115.5 (+)
unnamed: C152.1, R162.2, R163.1, U115.6 (-)
unnamed: C156.1, U116.2 (CAP+)
unnamed: C156.2, U116.4 (CAP-)
